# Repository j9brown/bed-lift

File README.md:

# Bed-lift controller

Controls a motorized bed-lift with two synchronized linear actuators for vertical lifting and lowering and two pairs of synchronized stepper motors for horizontal extension and retraction.  It fits in the back of a campervan.

## Circuit board revisions

Refer to the following documents for design synopsis, schematics, and circuit board illustrations.

- [v1](./hardware/v1/design-and-errata.md): Fixed errata, improved assignment of pin functions, added span limit hall sensors, buzzer and ESD protection
- [v0.2](./hardware/v0.2/design-and-errata.md): First feature-complete circuit board
- [v0.1](./hardware/v0.1/design-and-errata.md): Initial hand-assembled prototype

## About the "forklift" bed

This custom motorized bed fits in the back of a small campervan to allow dual-use of the living area in a standard wheelbase vehicle.  In its raised position, the bed platform is only supported from the back which gives it the appearance of a pallet on a forklift, hence the name.

To maximize space efficiency, the bed is designed for sleeping crosswise with the head and feet towards the sides of the vehicle.  This choice of sleeping orientation poses unique engineering challenges; it is more common to design lifting beds for sleeping lengthwise with the head and feet towards the front and back of the vehicle.

Because the van is narrower at roof elevantion than at sleeping elevation, the bed extends and retracts to span the gap between the main body of the bed platform and the sides of the vehicle.  The parts that extend and retract are called the bed wings (aka. wing spans).  The bed mattress is made of three cushions: one large central cushion on the main body of the bed platform and two narrower cushions that rest on the two bed wings.  The narrower cushions are removed and stowed on top of the bed before retracting the bed wings.

- When the bed is raised, the bed wings retract into the bed platform and the platform is cantilevered from steel columns attached to the rear doorframe and floor of the vehicle.

- When the bed is lowered, the bed wings extend from the bed platform and rest upon reinforced windowsills to transfer the load of the occupants to the vehicle walls.

The bed has limited load bearing capacity while raised so it must be lowered when occupied or while driving to prevent excess torque through the cantilever.  As an advantage, there are no cables, straps, bulkheads, guides, posts, or other obstructions in the front of the living area to support the bed.  As a disadvantage, the bed structure is heavy and difficult to build.

Feel free to contact me for advice if you are interested in building a bed like mine (and be prepared for a challenge)!

[Video tour of the v0.2 prototype](https://vimeo.com/1154513482/b7c7d3c8f7)

<details>
<summary>Photos of v0.2 prototype</summary>

### Bed lift in lowered position viewed from outside

### Bed lift in raised position viewed from outside

### Bed lift in lowered position viewed from inside

### Bed lift in raised position viewed from inside

### Bed lift controls

### Bed lift driver

### Bed lift position encoder

</details>

<details>
<summary>Photos of v0.1 prototype</summary>

### Bed lift in lowered position

### Bed lift in raised position

</details>

<details>
<summary>CAD model</summary>

### Bed lift in lowered position

### Bed lift in raised position

</details>

## How to build the firmware

The firmware is based on Zephyr RTOS v4.3 and compiled with `west`.

1. Install the Zephyr RTOS SDK tools.  You can either follow the [Zephyr Getting Started Guide](https://docs.zephyrproject.org/latest/develop/getting_started/index.html) or install an extension for your IDE, such as [Zephyr IDE](https://zephyr-ide.mylonics.com/) or [Workbench for Zephyr](https://z-workbench.com/), that can install the tools for you.

2. Install the [xPack OpenOCD](https://xpack-dev-tools.github.io/openocd-xpack/docs/install/) package for your OS and add it to your system `PATH`.  This step is needed because the version of OpenOCD that is distributed with Zephyr is too old and doesn't support the STM32C0x series of chips.  We need OpenOCD v0.12.0-7 at minimum.

3. Get the code and its dependencies.  This is a little more complicated than simply cloning this git repository because the Zephyr `west` multi-tool assumes that all of the code resides within a top directory called a workspace.  You will need to create an empty directory to be the workspace first.  Here's how to do it from the command-line and the same thing can be done with IDE extensions.

```sh
$ mkdir bed-lift-workspace
$ cd bed-lift-workspace
$ west init -m https://github.com/j9brown/bed-lift
$ west update
```

4. Build and the firmware (either release or debug).

```sh
$ cd bed-lift/firmware/app
$ west build -p -d build/release
$ west build -p -d build/debug -- -DFEATURE_LOG=y -DFEATURE_DEBUG=y
```

5. Connect an ST-Link v3 programmer to the `DEBUG` port with an `STDC14` cable.  Flash the firmware.

```sh
$ cd bed-lift/firmware/app
$ west flash
```

Firmware for the older prototypes is preserved in the git history.

- The v0.2 firmware was based on Zephyr RTOS v4.2.1 and compiled with Platform IO.
- The v0.1 firmware was based on Arduino and compiled with Platform IO.

## Usage

The lift control panel has three switches:

- `Power`: This on / off switch provides power to the lift driver and all actuators.  It is intended to remain on indefinitely.  Can be used to cut power in case of emergencies.
- `Up / Off / Down`: This momentary-on / off / momentary-on switch has two positions.  Toggling the switch to the `Up` position raises the lift to the lounge position.  Toggling the switch to the `Down` position lowers the lift to the sleeping position.  The switch must be held in the `Up` or `Down` position for 0.5 seconds to engage the actuators as a precaution against accidental triggering.  The lift stops moving immediately as soon as the switch is released and returns to the `Off` position.
- `Mode`: This momentary-on / off switch activates special modes.

By default, the lift starts on the `Main Menu` and the `Up / Off / Down` controls whether the lift moves into the lounge or sleep position.

While holding the switch `Up` or `Down` and the lift is raising or lowering, press the `Mode` button to activate automatic movement.  Then, release all of the controls and the lift will continue moving in the requested direction until the final position is reached or an error occurs.  To stop automatic movement, press any control.

**Use caution when activating automatic movement and continue paying attention to the lift to avoid damage or injury!**

to ensure the lift won't encounter any obstructions in this mode because it could damage itself if you aren't paying attention!

To access a different menu, press and hold the `Mode` button for 3 seconds until the indicator lights `Amber` then blinks one or more times in a different color and a tone is played.  The second color indicates the menu and the number of blinks indicates the action that will be performed when the `Up / Off / Down` switch is activated.  Press the `Mode` button to cycle among actions and observe the number of blinks change.  Press and hold the `Mode` button for 0.5 seconds to access the next menu and observe the blink color change.  Refer to the table below to identify the currently selected menu action.

The lift reverts to an idle state when the user does not interact with the controls for some time.

### Visual feedback

An RGB color indicator shows the state of the device at the control panel.  There is also a monochromatic red LED on the circuit board itself that indicators the same state as the indicator (but without color).

- When the lift remains idle for some time, the indicator turns off.
- When the lift is rising, the indicator shows a rainbow color wheel cycling from red to violet.
- When the lift is lowering, the indicator shows a rainbow color wheel cycling from violet to red.
- When the lift achieves the lounge or sleep position, the indicator lights `Green`.
- When the lift movement is aborted without achieving the lounge or sleep position, the indicator lights `Amber`.
- When a diagnostic menu mode is active, the indicator lights `Amber` then blinks one or more times in a different color depending on the menu.
- When an error occurs, the indicator lights `Red` then blinks one or more times in a different color depending on the error.

| Solid color  | Blink color  | Blinks | Purpose  | Meaning |
| ------------ | ------------ | ------ | -------- | ------- |
| Rainbow up   |              |        | Activity | Lift is rising |
| Rainbow down |              |        | Activity | Lift is lowering |
| Green        |              |        | Status   | Lift is in lounge or sleep position, ready for use |
| Amber        |              |        | Status   | Lift is in an intermediate position, not ready for use |
| Amber        | Cyan         | 1      | Menu     | Lift menu: Jog both lift actuators in tandem (synchronized) |
| Amber        | Cyan         | 2      | Menu     | Lift menu: Jog both lift actuators indepedently (not synchronized) |
| Amber        | Cyan         | 3      | Menu     | Lift menu: Jog lift actuator 1 (driver side) |
| Amber        | Cyan         | 4      | Menu     | Lift menu: Jog lift actuator 2 (passenger side) |
| Amber        | Blue         | 1      | Menu     | Span menu: Jog all span actuators in tandem (synchronized) |
| Amber        | Blue         | 2      | Menu     | Span menu: Jog both span actuators 1 and 2 (driver side) in tandem (synchronized) |
| Amber        | Blue         | 3      | Menu     | Span menu: Jog both span actuators 3 and 4 (passenger side) in tandem (synchronized) |
| Amber        | Blue         | 4      | Menu     | Span menu: Jog both span actuator 1 (front driver side) independently (not synchronized) |
| Amber        | Blue         | 5      | Menu     | Span menu: Jog both span actuator 2 (rear driver side) independently (not synchronized) |
| Amber        | Blue         | 6      | Menu     | Span menu: Jog both span actuator 3 (front passenger side) independently (not synchronized) |
| Amber        | Blue         | 7      | Menu     | Span menu: Jog both span actuator 4 (rear passenger side) independently (not synchronized) |
| Red          |              |        | Error    | Error: An unspecified error occurred |
| Red          | Magenta      | 1      | Error    | Control error: Movement of the bed has been remotely inhibited |
| Red          | Amber        | 1      | Error    | Bed error: The bed components are in an unknown or unexpected state |
| Red          | Cyan         | 1      | Error    | Lift error: Motor driver reported a fault |
| Red          | Cyan         | 2      | Error    | Lift error: The actuators lost synchronization |
| Red          | Cyan         | 3      | Error    | Lift error: Lift stationary when it should be moving or the hall sensors are not working correctly |
| Red          | Cyan         | 1      | Error    | Lift error: I/O error communicating with the motor driver |
| Red          | Cyan         | 1      | Error    | Lift error: Operation timed out because poll wasn't called often enough |
| Red          | Blue         | 1      | Error    | Span error: Motor driver reported a fault |
| Red          | Blue         | 2      | Error    | Span error: The actuators lost synchronization |
| Red          | Blue         | 3      | Error    | Span error: The actuators did not stall at their home position as expected |
| Red          | Blue         | 4      | Error    | Span error: The actuators traveled further than the expected distance without stalling |
| Red          | Blue         | 5      | Error    | Span error: I/O error communicating with the motor driver |
| Red          | Blue         | 6      | Error    | Span error: Operation timed out because poll wasn't called often enough |

### Audible feedback

A piezo buzzer provides audible feedback.

- When the lift successfully raises into the lounge position, it plays a brief fanfare that ends on a rising tone.
- When the lift successfully lowers into the sleep position, it plays a brief fanfare that ends on a falling tone.
- When the lift encounters an error, it plays three long tones as an alert.
- When the user attempts to perform an action that has been remotely inhibited, the lift plays three quick tones.
- When using the diagnostic menu, the lift plays a tone as each menu or mode is entered.

### I2C interface

Connect an I2C host to the lift driver's `EXT I2C` port using a `QWIIC` connector to remotely monitor the device, remotely inhibit operation of the control panel, and access low-level debug and test features.  The `EXT I2C` port galvanically isolates the bed lift from the host's power supply for safety.

Refer to [monitor.c](./firmware/app/src/monitor.c) for the I2C protocol implementation.

## Notice

The bed-lift software, documentation, design, and all copyright protected artifacts are released under the terms of the [MIT license](LICENSE).

The bed-lift hardware is released under the terms of the [CERN-OHL-W license](hardware/LICENSE).

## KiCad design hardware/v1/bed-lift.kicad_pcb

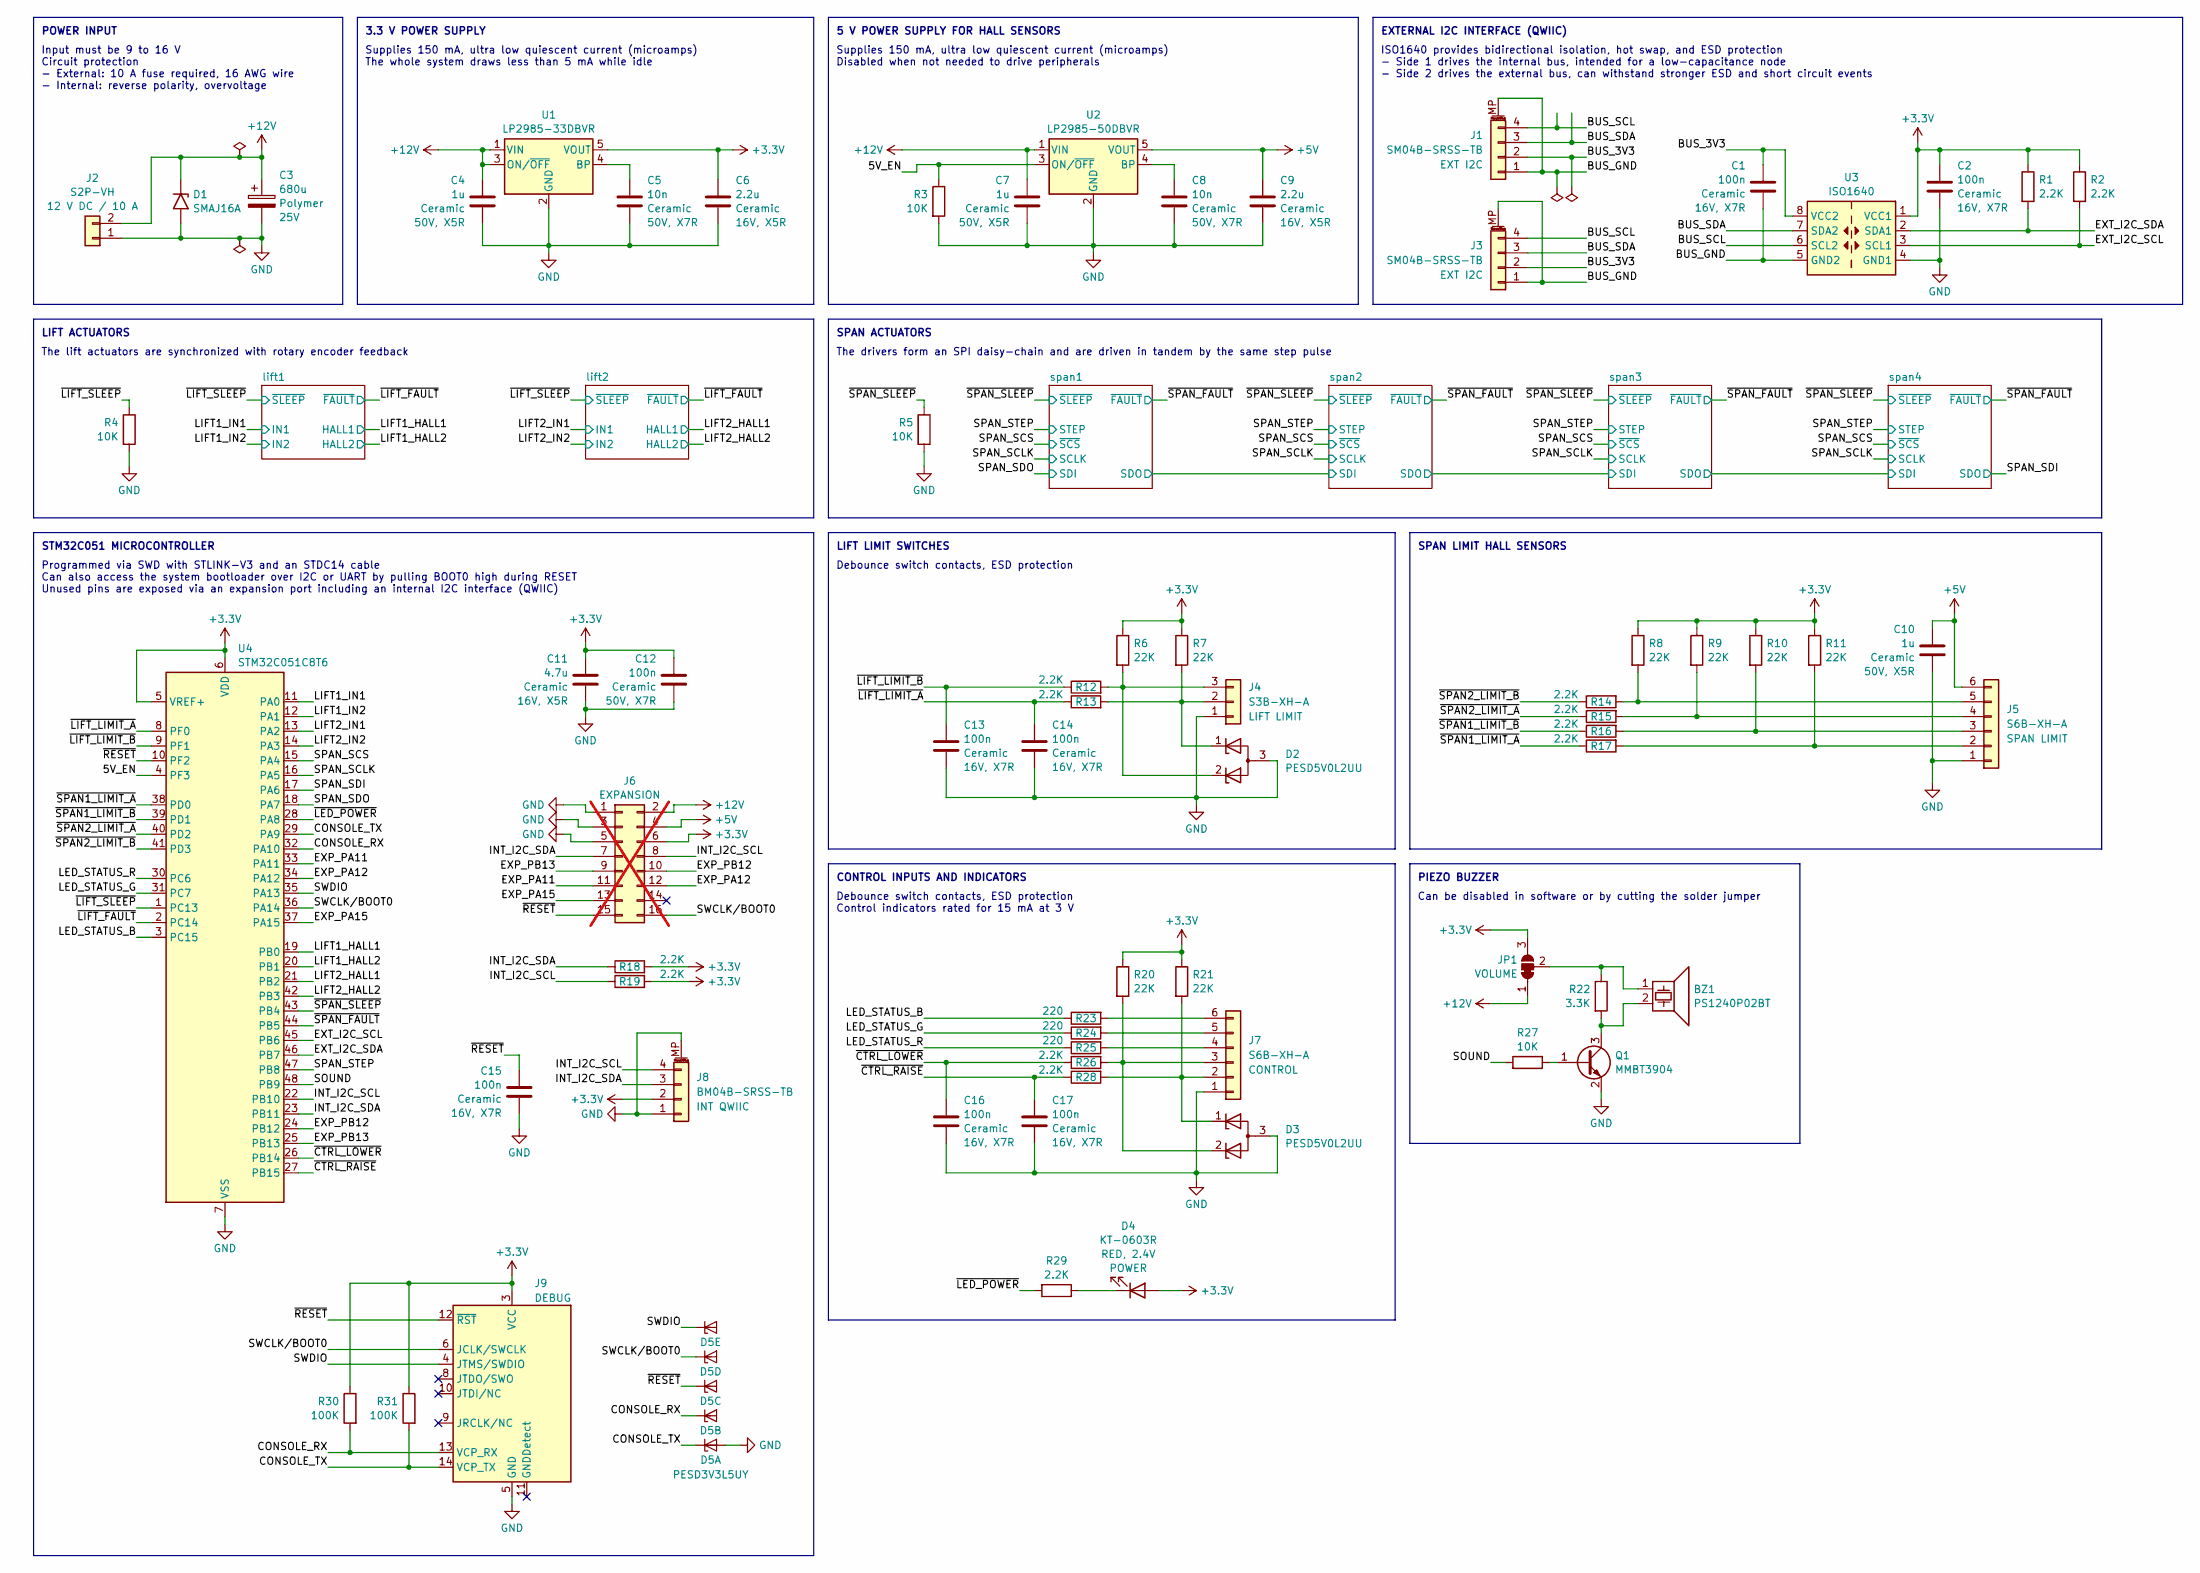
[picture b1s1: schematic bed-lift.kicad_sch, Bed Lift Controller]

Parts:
BZ1: PS1240P02BT; Buzzer_TDK_PS1240P02BT_D12.2mm_H6.5mm; LCSC C76871
C1, C2, C13, C14, C15, C16, C17: 100n; C_0402_1005Metric; Rating 16V, X7R; LCSC C1525
C3: 680u; CP_Radial_D8.0mm_P3.50mm; Rating 25V; Part Alternative A750KW687M1EAAE016; LCSC C5243855
C4, C7, C10: 1u; C_0603_1608Metric; Rating 50V, X5R; LCSC C15849
C5, C8: 10n; C_0402_1005Metric; Rating 50V, X7R; LCSC C15195
C6, C9: 2.2u; C_0603_1608Metric; Rating 16V, X5R; LCSC C23630
C11: 4.7u; C_0603_1608Metric; Rating 16V, X5R; LCSC C19666
C12: 100n; C_0603_1608Metric; Rating 50V, X7R; LCSC C14663
D1: SMAJ16A; D_SMA; LCSC C74561
D2, D3: PESD5V0L2UU; SOT-323_SC-70; LCSC C78769
D4: KT-0603R; LED_0603_1608Metric; Rating RED, 2.4V; LCSC C2286
D5: PESD3V3L5UY; SOT-363_SC-70-6; LCSC C3021133
J1, J3: SM04B-SRSS-TB; JST_SH_SM04B-SRSS-TB_1x04-1MP_P1.00mm_Horizontal; Part Alternative GT-A1002WRS-104SBT01; LCSC C160404
J2: S2P-VH; JST_VH_S2P-VH_1x02_P3.96mm_Horizontal; LCSC C160355
J4: S3B-XH-A; JST_XH_S3B-XH-A_1x03_P2.50mm_Horizontal; LCSC C157928
J5, J7: S6B-XH-A; JST_XH_S6B-XH-A_1x06_P2.50mm_Horizontal; LCSC C157919
J6: Conn_02x08_Odd_Even; PinSocket_2x08_P2.54mm_Vertical; not fitted
J8: BM04B-SRSS-TB; JST_SH_BM04B-SRSS-TB_1x04-1MP_P1.00mm_Vertical; LCSC C160390
J9: Conn_ST_STDC14; SAMTEC_FTSH-107-01-L-DV-K-A; LCSC C5563894
JP1: SolderJumper_3_Bridged12; SolderJumper-3_P1.3mm_Bridged12_RoundedPad1.0x1.5mm
Q1: MMBT3904; SOT-23; LCSC C20526
R1, R2, R12, R13, R14, R15, R16, R17, R18, R19, R26, R28, R29: 2.2K; R_0402_1005Metric; LCSC C25879
R3, R4, R5, R27: 10K; R_0402_1005Metric; LCSC C25744
R6, R7, R8, R9, R10, R11, R20, R21: 22K; R_0402_1005Metric; LCSC C25768
R22: 3.3K; R_0603_1608Metric; LCSC C22978
R23, R24, R25: 220; R_0402_1005Metric; LCSC C25091
R30, R31: 100K; R_0402_1005Metric; LCSC C25741
U1: LP2985-33DBVR; SOT-23-5; LCSC C95414
U2: LP2985-50DBVR; SOT-23-5; LCSC C74511
U3: ISO1640; SOIC-8_3.9x4.9mm_P1.27mm; LCSC C5122339
U4: STM32C051C8T6; LQFP-48_7x7mm_P0.5mm; LCSC C45870050

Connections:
+3.3V: C2.1, C6.2, C11.1, C12.1, D4.2 (A), J6.6, J8.2, J9.3 (VCC), JP1.3 (B), R1.1, R2.1, R6.1, R7.1, R8.1, R9.1, R10.1, R11.1, R18.2, R19.2, R20.1, R21.1, R30.1, R31.1, U1.5 (VOUT), U3.1 (VCC1), U4.5 (VREF+), U4.6 (VDD); also elsewhere on the board
+5V: C9.2, C10.1, J5.6, J6.4, U2.5 (VOUT); also elsewhere on the board
+12V: C3.1, C4.1, C7.1, D1.1 (A1), J2.2, J6.2, JP1.1 (A), U1.1 (VIN), U1.3 (ON/~OFF), U2.1 (VIN); also elsewhere on the board
/5V_EN: R3.1, U2.3 (ON/~OFF), U4.4 (PF3)
/BUS_3V3: C1.1, J1.2, J3.2, U3.8 (VCC2)
/BUS_GND: C1.2, J1.1, J1.MP (MountPin), J3.1, J3.MP (MountPin), U3.5 (GND2)
/BUS_SCL: J1.4, J3.4, U3.6 (SCL2)
/BUS_SDA: J1.3, J3.3, U3.7 (SDA2)
/CONSOLE_RX: D5.3 (K2), J9.13 (VCP_RX), R30.2, U4.32 (PA10)
/CONSOLE_TX: D5.1 (K1), J9.14 (VCP_TX), R31.2, U4.29 (PA9)
/EXP_PA11: J6.11, U4.33 (PA11)
/EXP_PA12: J6.12, U4.34 (PA12)
/EXP_PA15: J6.13, U4.37 (PA15)
/EXP_PB12: J6.10, U4.24 (PB12)
/EXP_PB13: J6.9, U4.25 (PB13)
/EXT_I2C_SCL: R2.2, U3.3 (SCL1), U4.45 (PB6)
/EXT_I2C_SDA: R1.2, U3.2 (SDA1), U4.46 (PB7)
/INT_I2C_SCL: J6.8, J8.4, R19.1, U4.22 (PB10)
/INT_I2C_SDA: J6.7, J8.3, R18.1, U4.23 (PB11)
/LED_STATUS_B: R23.1, U4.3 (PC15)
/LED_STATUS_G: R24.1, U4.31 (PC7)
/LED_STATUS_R: R25.1, U4.30 (PC6)
/LIFT1_HALL1: U4.19 (PB0); also elsewhere on the board
/LIFT1_HALL2: U4.20 (PB1); also elsewhere on the board
/LIFT1_IN1: U4.11 (PA0); also elsewhere on the board
/LIFT1_IN2: U4.12 (PA1); also elsewhere on the board
/LIFT2_HALL1: U4.21 (PB2); also elsewhere on the board
/LIFT2_HALL2: U4.42 (PB3); also elsewhere on the board
/LIFT2_IN1: U4.13 (PA2); also elsewhere on the board
/LIFT2_IN2: U4.14 (PA3); also elsewhere on the board
/SOUND: R27.2, U4.48 (PB9)
/SPAN_SCLK: U4.16 (PA5); also elsewhere on the board
/SPAN_SCS: U4.15 (PA4); also elsewhere on the board
/SPAN_SDI: U4.17 (PA6); also elsewhere on the board
/SPAN_SDO: U4.18 (PA7); also elsewhere on the board
/SPAN_STEP: U4.47 (PB8); also elsewhere on the board
/SWCLK/BOOT0: D5.5 (K4), J6.16, J9.6 (JCLK/SWCLK), U4.36 (PA14)
/SWDIO: D5.6 (K5), J9.4 (JTMS/SWDIO), U4.35 (PA13)
/~CTRL_LOWER: C16.1, R26.1, U4.26 (PB14)
/~CTRL_RAISE: C17.1, R28.1, U4.27 (PB15)
/~LED_POWER: R29.2, U4.28 (PA8)
/~LIFT_FAULT: U4.2 (PC14); also elsewhere on the board
/~LIFT_LIMIT_A: C14.1, R13.1, U4.8 (PF0)
/~LIFT_LIMIT_B: C13.1, R12.1, U4.9 (PF1)
/~LIFT_SLEEP: R4.1, U4.1 (PC13); also elsewhere on the board
/~RESET: C15.1, D5.4 (K3), J6.15, J9.12 (~RST), U4.10 (PF2)
/~SPAN1_LIMIT_A: R17.1, U4.38 (PD0)
/~SPAN1_LIMIT_B: R16.1, U4.39 (PD1)
/~SPAN2_LIMIT_A: R15.1, U4.40 (PD2)
/~SPAN2_LIMIT_B: R14.1, U4.41 (PD3)
/~SPAN_FAULT: U4.44 (PB5); also elsewhere on the board
/~SPAN_SLEEP: R5.1, U4.43 (PB4); also elsewhere on the board
GND: C2.2, C3.2, C4.2, C5.1, C6.1, C7.2, C8.1, C9.1, C10.2, C11.2, C12.2, C13.2, C14.2, C15.2, C16.2, C17.2, D1.2 (A2), D2.3 (A), D3.3 (A), D5.2 (A), J2.1, J4.1, J5.1, J6.1, J6.3, J6.5, J7.1, J8.1, J8.MP (MountPin), J9.5 (GND), J9.7 (GND), Q1.2 (E), R3.2, R4.2, R5.2, U1.2 (GND), U2.2 (GND), U3.4 (GND1), U4.7 (VSS); also elsewhere on the board
unnamed: D4.1 (K), R29.1
unnamed: D2.1 (K), J4.2, R7.2, R13.2
unnamed: D2.2 (K), J4.3, R6.2, R12.2
unnamed: J5.2, R11.2, R17.2
unnamed: J5.3, R10.2, R16.2
unnamed: J5.4, R9.2, R15.2
unnamed: J5.5, R8.2, R14.2
unnamed: D3.1 (K), J7.2, R21.2, R28.2
unnamed: D3.2 (K), J7.3, R20.2, R26.2
unnamed: J7.4, R25.2
unnamed: J7.5, R24.2
unnamed: J7.6, R23.2
unnamed: BZ1.1, JP1.2 (C), R22.1
unnamed: Q1.1 (B), R27.1
unnamed: BZ1.2, Q1.3 (C), R22.2
unnamed: C5.2, U1.4 (BP)
unnamed: C8.2, U2.4 (BP)

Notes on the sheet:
Programmed via SWD with STLINK-V3 and an STDC14 cable Can also access the system bootloader over I2C or UART by pulling BOOT0 high during RESET Unused pins are exposed via an expansion port including an internal I2C interface (QWIIC)
Supplies 150 mA, ultra low quiescent current (microamps) The whole system draws less than 5 mA while idle
LIFT LIMIT SWITCHES
POWER INPUT
5 V POWER SUPPLY FOR HALL SENSORS
The lift actuators are synchronized with rotary encoder feedback
SPAN ACTUATORS
Can be disabled in software or by cutting the solder jumper
STM32C051 MICROCONTROLLER
3.3 V POWER SUPPLY
Supplies 150 mA, ultra low quiescent current (microamps) Disabled when not needed to drive peripherals
EXTERNAL I2C INTERFACE (QWIIC)
SPAN LIMIT HALL SENSORS
PIEZO BUZZER
The drivers form an SPI daisy-chain and are driven in tandem by the same step pulse
CONTROL INPUTS AND INDICATORS
Input must be 9 to 16 V Circuit protection - External: 10 A fuse required, 16 AWG wire - Internal: reverse polarity, overvoltage
ISO1640 provides bidirectional isolation, hot swap, and ESD protection - Side 1 drives the internal bus, intended for a low-capacitance node - Side 2 drives the external bus, can withstand stronger ESD and short circuit events
LIFT ACTUATORS
Debounce switch contacts, ESD protection Control indicators rated for 15 mA at 3 V
Debounce switch contacts, ESD protection

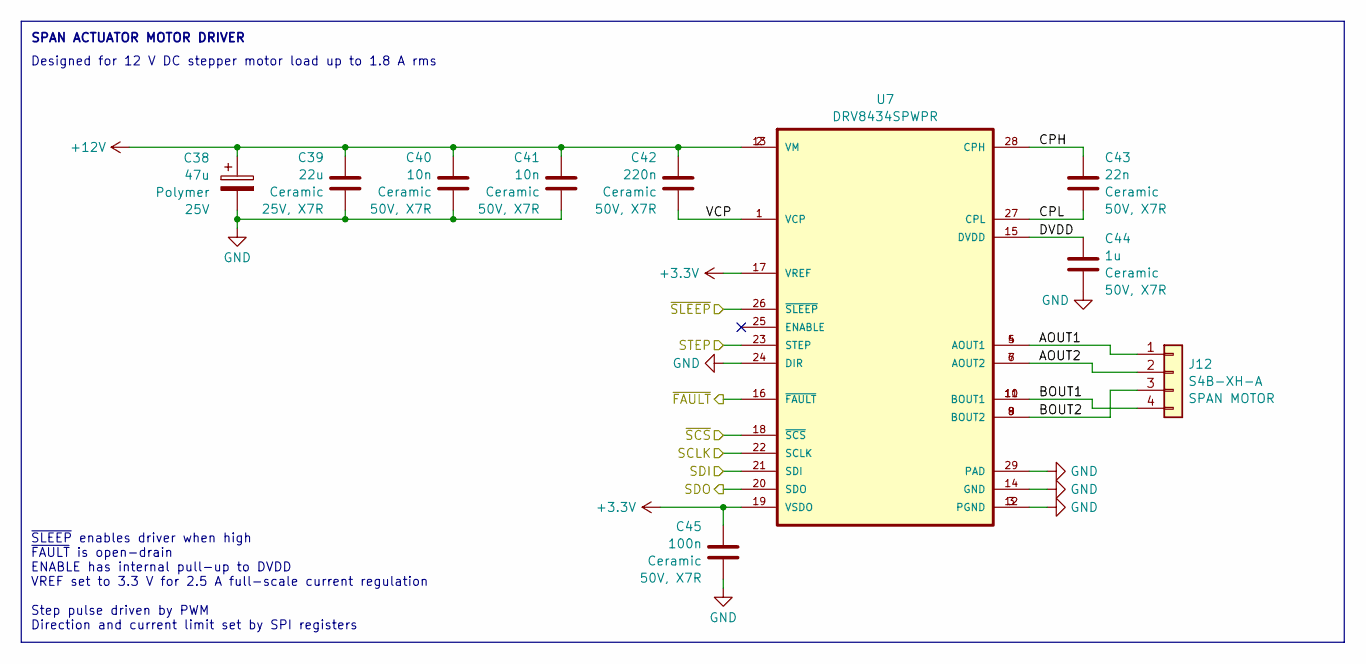
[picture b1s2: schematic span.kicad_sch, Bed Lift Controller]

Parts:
C38: 47u; CP_Radial_D5.0mm_P2.50mm; Rating 25V; Part 4700250508R00; LCSC C5243872
C39: 22u; C_1210_3225Metric; Rating 25V, X7R; LCSC C309062
C40, C41: 10n; C_0603_1608Metric; Rating 50V, X7R; LCSC C57112
C42: 220n; C_0603_1608Metric; Rating 50V, X7R; LCSC C21120
C43: 22n; C_0603_1608Metric; Rating 50V, X7R; LCSC C21122
C44: 1u; C_0805_2012Metric; Rating 50V, X7R; LCSC C28323
C45: 100n; C_0603_1608Metric; Rating 50V, X7R; LCSC C14663
J12: S4B-XH-A; JST_XH_S4B-XH-A_1x04_P2.50mm_Horizontal; LCSC C157925
U7: DRV8434SPWPR; HTSSOP-28 PWP0028M; LCSC C3681202

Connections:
+3.3V: C45.1, U7.17 (VREF), U7.19 (VSDO); also elsewhere on the board
+12V: C38.1, C39.2, C40.1, C41.1, C42.1, U7.2 (VM), U7.13 (VM); also elsewhere on the board
/SPAN_SCLK: U7.22 (SCLK); also elsewhere on the board
/SPAN_SCS: U7.18 (~SCS); also elsewhere on the board
/SPAN_SDO: U7.21 (SDI); also elsewhere on the board
/SPAN_STEP: U7.23 (STEP); also elsewhere on the board
/span1/AOUT1: J12.1, U7.4 (AOUT1), U7.5 (AOUT1)
/span1/AOUT2: J12.2, U7.6 (AOUT2), U7.7 (AOUT2)
/span1/BOUT1: J12.4, U7.10 (BOUT1), U7.11 (BOUT1)
/span1/BOUT2: J12.3, U7.8 (BOUT2), U7.9 (BOUT2)
/span1/CPH: C43.1, U7.28 (CPH)
/span1/CPL: C43.2, U7.27 (CPL)
/span1/DVDD: C44.1, U7.15 (DVDD)
/span1/SDO: U7.20 (SDO); also elsewhere on the board
/span1/VCP: C42.2, U7.1 (VCP)
/~SPAN_FAULT: U7.16 (~FAULT); also elsewhere on the board
/~SPAN_SLEEP: U7.26 (~SLEEP); also elsewhere on the board
GND: C38.2, C39.1, C40.2, C41.2, C44.2, C45.2, U7.3 (PGND), U7.12 (PGND), U7.14 (GND), U7.24 (DIR), U7.29 (PAD); also elsewhere on the board

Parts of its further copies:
C46, C54, C62: 47u; CP_Radial_D5.0mm_P2.50mm; Rating 25V; Part 4700250508R00; LCSC C5243872
C47, C55, C63: 22u; C_1210_3225Metric; Rating 25V, X7R; LCSC C309062
C48, C49, C56, C57, C64, C65: 10n; C_0603_1608Metric; Rating 50V, X7R; LCSC C57112
C50, C58, C66: 220n; C_0603_1608Metric; Rating 50V, X7R; LCSC C21120
C51, C59, C67: 22n; C_0603_1608Metric; Rating 50V, X7R; LCSC C21122
C52, C60, C68: 1u; C_0805_2012Metric; Rating 50V, X7R; LCSC C28323
C53, C61, C69: 100n; C_0603_1608Metric; Rating 50V, X7R; LCSC C14663
J13, J14, J15: S4B-XH-A; JST_XH_S4B-XH-A_1x04_P2.50mm_Horizontal; LCSC C157925
U8, U9, U10: DRV8434SPWPR; HTSSOP-28 PWP0028M; LCSC C3681202

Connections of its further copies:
+3.3V: C53.1, C61.1, C69.1, U8.17 (VREF), U8.19 (VSDO), U9.17 (VREF), U9.19 (VSDO), U10.17 (VREF), U10.19 (VSDO); also elsewhere on the board
+12V: C46.1, C47.2, C48.1, C49.1, C50.1, C54.1, C55.2, C56.1, C57.1, C58.1, C62.1, C63.2, C64.1, C65.1, C66.1, U8.2 (VM), U8.13 (VM), U9.2 (VM), U9.13 (VM), U10.2 (VM), U10.13 (VM); also elsewhere on the board
/SPAN_SCLK: U8.22 (SCLK), U9.22 (SCLK), U10.22 (SCLK); also elsewhere on the board
/SPAN_SCS: U8.18 (~SCS), U9.18 (~SCS), U10.18 (~SCS); also elsewhere on the board
/SPAN_SDI: U10.20 (SDO); also elsewhere on the board
/SPAN_STEP: U8.23 (STEP), U9.23 (STEP), U10.23 (STEP); also elsewhere on the board
/span1/SDO: U8.21 (SDI); also elsewhere on the board
/span2/AOUT1: J13.1, U8.4 (AOUT1), U8.5 (AOUT1)
/span2/AOUT2: J13.2, U8.6 (AOUT2), U8.7 (AOUT2)
/span2/BOUT1: J13.4, U8.10 (BOUT1), U8.11 (BOUT1)
/span2/BOUT2: J13.3, U8.8 (BOUT2), U8.9 (BOUT2)
/span2/CPH: C51.1, U8.28 (CPH)
/span2/CPL: C51.2, U8.27 (CPL)
/span2/DVDD: C52.1, U8.15 (DVDD)
/span2/SDO: U8.20 (SDO), U9.21 (SDI)
/span2/VCP: C50.2, U8.1 (VCP)
/span3/AOUT1: J14.1, U9.4 (AOUT1), U9.5 (AOUT1)
/span3/AOUT2: J14.2, U9.6 (AOUT2), U9.7 (AOUT2)
/span3/BOUT1: J14.4, U9.10 (BOUT1), U9.11 (BOUT1)
/span3/BOUT2: J14.3, U9.8 (BOUT2), U9.9 (BOUT2)
/span3/CPH: C59.1, U9.28 (CPH)
/span3/CPL: C59.2, U9.27 (CPL)
/span3/DVDD: C60.1, U9.15 (DVDD)
/span3/SDO: U9.20 (SDO), U10.21 (SDI)
/span3/VCP: C58.2, U9.1 (VCP)
/span4/AOUT1: J15.1, U10.4 (AOUT1), U10.5 (AOUT1)
/span4/AOUT2: J15.2, U10.6 (AOUT2), U10.7 (AOUT2)
/span4/BOUT1: J15.4, U10.10 (BOUT1), U10.11 (BOUT1)
/span4/BOUT2: J15.3, U10.8 (BOUT2), U10.9 (BOUT2)
/span4/CPH: C67.1, U10.28 (CPH)
/span4/CPL: C67.2, U10.27 (CPL)
/span4/DVDD: C68.1, U10.15 (DVDD)
/span4/VCP: C66.2, U10.1 (VCP)
/~SPAN_FAULT: U8.16 (~FAULT), U9.16 (~FAULT), U10.16 (~FAULT); also elsewhere on the board
/~SPAN_SLEEP: U8.26 (~SLEEP), U9.26 (~SLEEP), U10.26 (~SLEEP); also elsewhere on the board
GND: C46.2, C47.1, C48.2, C49.2, C52.2, C53.2, C54.2, C55.1, C56.2, C57.2, C60.2, C61.2, C62.2, C63.1, C64.2, C65.2, C68.2, C69.2, U8.3 (PGND), U8.12 (PGND), U8.14 (GND), U8.24 (DIR), U8.29 (PAD), U9.3 (PGND), U9.12 (PGND), U9.14 (GND), U9.24 (DIR), U9.29 (PAD), U10.3 (PGND), U10.12 (PGND), U10.14 (GND), U10.24 (DIR), U10.29 (PAD); also elsewhere on the board

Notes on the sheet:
Designed for 12 V DC stepper motor load up to 1.8 A rms
SPAN ACTUATOR MOTOR DRIVER
~{SLEEP} enables driver when high ~{FAULT} is open-drain ENABLE has internal pull-up to DVDD VREF set to 3.3 V for 2.5 A full-scale current regulation Step pulse driven by PWM Direction and current limit set by SPI registers

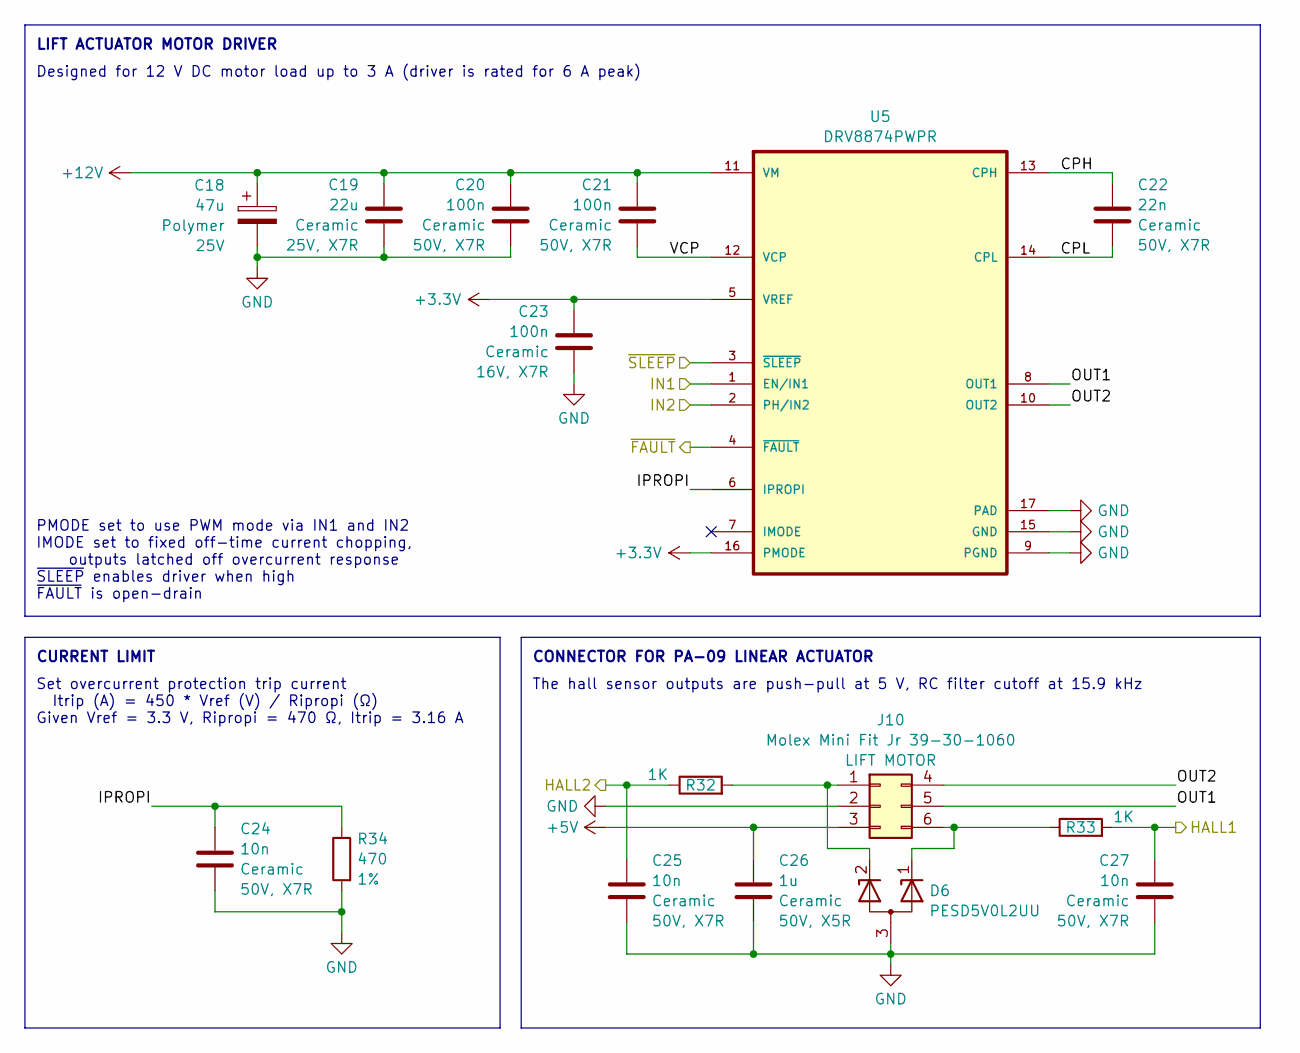
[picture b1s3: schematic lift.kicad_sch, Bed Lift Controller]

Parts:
C18: 47u; CP_Radial_D5.0mm_P2.50mm; Rating 25V; Part 4700250508R00; LCSC C5243872
C19: 22u; C_1210_3225Metric; Rating 25V, X7R; LCSC C309062
C20, C21: 100n; C_0603_1608Metric; Rating 50V, X7R; LCSC C14663
C22: 22n; C_0603_1608Metric; Rating 50V, X7R; LCSC C21122
C23: 100n; C_0402_1005Metric; Rating 16V, X7R; LCSC C1525
C24, C25, C27: 10n; C_0402_1005Metric; Rating 50V, X7R; LCSC C15195
C26: 1u; C_0603_1608Metric; Rating 50V, X5R; LCSC C15849
D6: PESD5V0L2UU; SOT-323_SC-70; LCSC C78769
J10: Molex Mini Fit Jr 39-30-1060; MOLEX_39301060; LCSC C114098
R32, R33: 1K; R_0402_1005Metric; LCSC C11702
R34: 470; R_0402_1005Metric; Rating 1%; LCSC C25117
U5: DRV8874PWPR; HTSSOP-16 PWP0016J; LCSC C1855818

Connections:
+3.3V: C23.1, U5.5 (VREF), U5.16 (PMODE); also elsewhere on the board
+5V: C26.1, J10.3; also elsewhere on the board
+12V: C18.1, C19.2, C20.1, C21.1, U5.11 (VM); also elsewhere on the board
/LIFT1_HALL1: C27.1, R33.2; also elsewhere on the board
/LIFT1_HALL2: C25.1, R32.1; also elsewhere on the board
/LIFT1_IN1: U5.1 (EN/IN1); also elsewhere on the board
/LIFT1_IN2: U5.2 (PH/IN2); also elsewhere on the board
/lift1/CPH: C22.1, U5.13 (CPH)
/lift1/CPL: C22.2, U5.14 (CPL)
/lift1/IPROPI: C24.1, R34.1, U5.6 (IPROPI)
/lift1/OUT1: J10.5, U5.8 (OUT1)
/lift1/OUT2: J10.4, U5.10 (OUT2)
/lift1/VCP: C21.2, U5.12 (VCP)
/~LIFT_FAULT: U5.4 (~FAULT); also elsewhere on the board
/~LIFT_SLEEP: U5.3 (~SLEEP); also elsewhere on the board
GND: C18.2, C19.1, C20.2, C23.2, C24.2, C25.2, C26.2, C27.2, D6.3 (A), J10.2, R34.2, U5.9 (PGND), U5.15 (GND), U5.17 (PAD); also elsewhere on the board
unnamed: D6.2 (K), J10.1, R32.2
unnamed: D6.1 (K), J10.6, R33.1

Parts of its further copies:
C28: 47u; CP_Radial_D5.0mm_P2.50mm; Rating 25V; Part 4700250508R00; LCSC C5243872
C29: 22u; C_1210_3225Metric; Rating 25V, X7R; LCSC C309062
C30, C31: 100n; C_0603_1608Metric; Rating 50V, X7R; LCSC C14663
C32: 22n; C_0603_1608Metric; Rating 50V, X7R; LCSC C21122
C33: 100n; C_0402_1005Metric; Rating 16V, X7R; LCSC C1525
C34, C35, C37: 10n; C_0402_1005Metric; Rating 50V, X7R; LCSC C15195
C36: 1u; C_0603_1608Metric; Rating 50V, X5R; LCSC C15849
D7: PESD5V0L2UU; SOT-323_SC-70; LCSC C78769
J11: Molex Mini Fit Jr 39-30-1060; MOLEX_39301060; LCSC C114098
R35, R36: 1K; R_0402_1005Metric; LCSC C11702
R37: 470; R_0402_1005Metric; Rating 1%; LCSC C25117
U6: DRV8874PWPR; HTSSOP-16 PWP0016J; LCSC C1855818

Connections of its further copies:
+3.3V: C33.1, U6.5 (VREF), U6.16 (PMODE); also elsewhere on the board
+5V: C36.1, J11.3; also elsewhere on the board
+12V: C28.1, C29.2, C30.1, C31.1, U6.11 (VM); also elsewhere on the board
/LIFT2_HALL1: C37.1, R36.2; also elsewhere on the board
/LIFT2_HALL2: C35.1, R35.1; also elsewhere on the board
/LIFT2_IN1: U6.1 (EN/IN1); also elsewhere on the board
/LIFT2_IN2: U6.2 (PH/IN2); also elsewhere on the board
/lift2/CPH: C32.1, U6.13 (CPH)
/lift2/CPL: C32.2, U6.14 (CPL)
/lift2/IPROPI: C34.1, R37.1, U6.6 (IPROPI)
/lift2/OUT1: J11.5, U6.8 (OUT1)
/lift2/OUT2: J11.4, U6.10 (OUT2)
/lift2/VCP: C31.2, U6.12 (VCP)
/~LIFT_FAULT: U6.4 (~FAULT); also elsewhere on the board
/~LIFT_SLEEP: U6.3 (~SLEEP); also elsewhere on the board
GND: C28.2, C29.1, C30.2, C33.2, C34.2, C35.2, C36.2, C37.2, D7.3 (A), J11.2, R37.2, U6.9 (PGND), U6.15 (GND), U6.17 (PAD); also elsewhere on the board
unnamed: D7.2 (K), J11.1, R35.2
unnamed: D7.1 (K), J11.6, R36.1

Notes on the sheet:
CONNECTOR FOR PA-09 LINEAR ACTUATOR
PMODE set to use PWM mode via IN1 and IN2 IMODE set to fixed off-time current chopping, outputs latched off overcurrent response ~{SLEEP} enables driver when high ~{FAULT} is open-drain
LIFT ACTUATOR MOTOR DRIVER
CURRENT LIMIT
Designed for 12 V DC motor load up to 3 A (driver is rated for 6 A peak)
Set overcurrent protection trip current Itrip (A) = 450 * Vref (V) / Ripropi (Ω) Given Vref = 3.3 V, Ripropi = 470 Ω, Itrip = 3.16 A
The hall sensor outputs are push-pull at 5 V, RC filter cutoff at 15.9 kHz

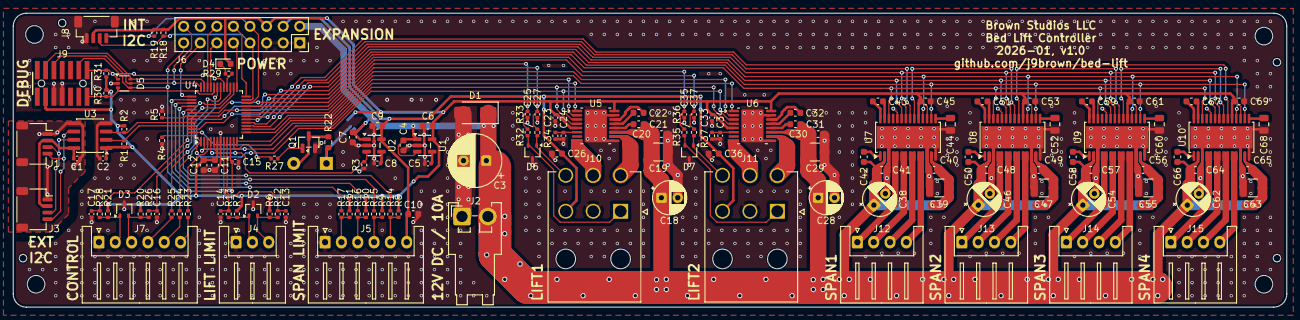
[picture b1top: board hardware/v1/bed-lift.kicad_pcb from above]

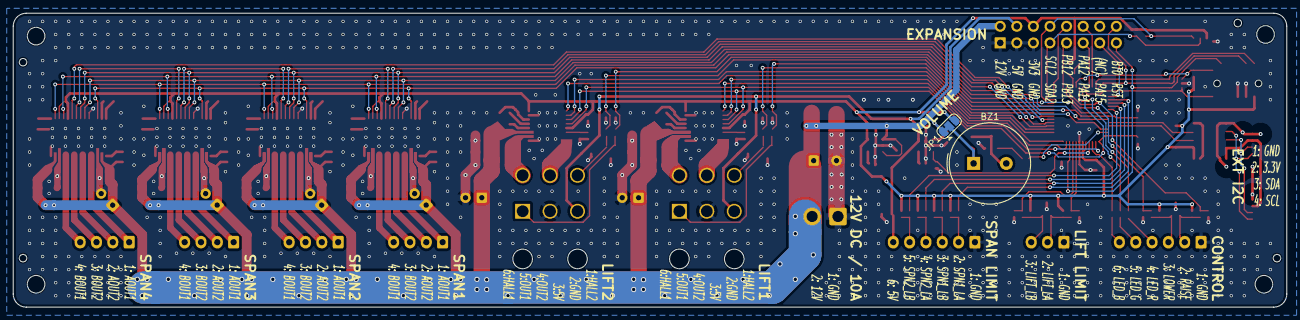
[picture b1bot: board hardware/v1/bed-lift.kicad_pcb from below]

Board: 4 copper layers, 195.0 x 45.0 mm, 149 parts (2 on the bottom side), 121 nets.

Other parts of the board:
MP1, MP2, MP3, MP4: MountingHole_2.7mm_M2.5
TH1, TH1#2, TH1#3, TH1#4: JLCPCB_PCBA_Tooling_Hole
